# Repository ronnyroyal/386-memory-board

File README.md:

# 386 memory board by ronnyroy

This is an attempt to reproduce and improve the 32 bit memory expansion cards of the Intel 301 386 mainboard https://theretroweb.com/motherboards/s/intel-301-system-board-pba-451213-xxx based off my original 2MB card.  
Instead of 41256 DIP DRAM chips it uses 30pin SIMM modules, all SMD parts and can also be adapted to 8MB.  

Big thanks to i440bx who was working on reverse engineering his own card independently and helped greatly by finding the user manual for the board and an image of the 8MB card on https://www.vaxbarn.com/index.php?option=com_content&view=article&id=749.

# Initial Revision
The initial PCB revision has been tested and confirmed working.  
It was designed to test my clone of the 2MB card and for modding it to 8MB.

### Modding to 8MB
- CPUA21(pin85) on the slot to pin 5 of U9 and U16.  
- CPUA22(pin95) on the slot to pin 4 of U10 and U13.

# Second Revision
This adds the missing traces and jumpers required for 2/8MB operation and the slot cutout i excluded from rev.1.  

# Important!
An 8MB card configured to 2MB on the mainboard will start up fine and even pass an extended CheckIt memory test but running programs that use the memory of the card crash.  
So the card needs to be configured matching to the mainboard.

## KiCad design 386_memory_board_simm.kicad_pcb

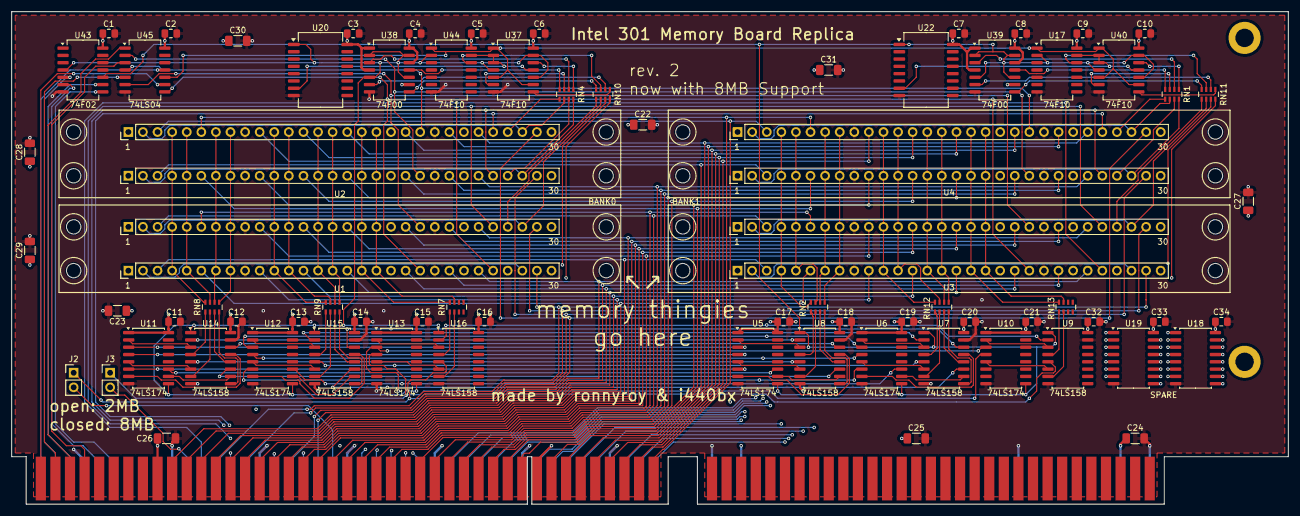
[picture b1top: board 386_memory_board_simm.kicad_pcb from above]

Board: 4 copper layers, 222.2 x 85.7 mm, 77 parts (0 on the bottom side), 174 nets.

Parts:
C1, C2, C3, C4, C5, C6, C7, C8, C9, C10, C11, C12, C13, C14, C15, C16, C17, C18, C19, C20, C21, C32, C33, C34: 100nF; C_0805_2012Metric_Pad1.18x1.45mm_HandSolder
C22, C23, C24, C25, C26, C27, C28, C29, C30, C31: 10µF; C_1206_3216Metric_Pad1.33x1.80mm_HandSolder
H1, H2: MountingHole; MountingHole_3.2mm_M3_DIN965_Pad
J1: Bus_386_Memory; BUS_386_MEMORY
J2, J3: Conn_01x02_Pin; PinHeader_1x02_P2.54mm_Vertical
RN1, RN2, RN4, RN7, RN8, RN9, RN10, RN11, RN12, RN13: 33Ω; R_Array_Concave_4x0603
U1, U2, U3, U4: DOUBLE-SIMM-30
U5, U6, U10, U11, U12, U13: 74LS174; SO-16_5.3x10.2mm_P1.27mm
U7, U8, U9, U14, U15, U16: 74LS158; SO-16_5.3x10.2mm_P1.27mm
U17, U37, U40, U44: 74F10; SO-14_5.3x10.2mm_P1.27mm
U18, U19: SPARE; SO-16_5.3x10.2mm_P1.27mm
U20, U22: SOIC-16W_7.5x12.8mm_P1.27mm
U38, U39: 74F00; SO-14_5.3x10.2mm_P1.27mm
U43: 74F02; SO-14_5.3x10.2mm_P1.27mm
U45: 74LS04; SO-14_5.3x10.2mm_P1.27mm

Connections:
A0A: J1.63 (CPUA3), U8.2 (I0a), U14.2 (I0a)
A0B: J1.70 (CPUA12), U5.3 (D0), U11.3 (D0)
A0B0: RN8.8 (R1.2), U1.4A (A0A), U1.4B (A0B), U2.4A (A0A), U2.4B (A0B)
A0B1: RN2.8 (R1.2), U3.4A (A0A), U3.4B (A0B), U4.4A (A0A), U4.4B (A0B)
A1A: J1.64 (CPUA4), U8.5 (I0b), U14.5 (I0b)
A1B: J1.71 (CPUA13), U5.4 (D1), U11.4 (D1)
A1B0: RN8.7 (R2.2), U1.5A (A1A), U1.5B (A1B), U2.5A (A1A), U2.5B (A1B)
A1B1: RN2.7 (R2.2), U3.5A (A1A), U3.5B (A1B), U4.5A (A1A), U4.5B (A1B)
A2A: J1.65 (CPUA5), U8.14 (I0c), U14.14 (I0c)
A2B: J1.73 (CPUA14), U5.6 (D2), U11.6 (D2)
A2B0: RN8.6 (R3.2), U1.7A (A2A), U1.7B (A2B), U2.7A (A2A), U2.7B (A2B)
A2B1: RN2.6 (R3.2), U3.7A (A2A), U3.7B (A2B), U4.7A (A2A), U4.7B (A2B)
A3A: J1.67 (CPUA6), U8.11 (I0d), U14.11 (I0d)
A3B: J1.74 (CPUA15), U5.11 (D3), U11.11 (D3)
A3B0: RN8.5 (R4.2), U1.8A (A3A), U1.8B (A3B), U2.8A (A3A), U2.8B (A3B)
A3B1: RN2.5 (R4.2), U3.8A (A3A), U3.8B (A3B), U4.8A (A3A), U4.8B (A3B)
A4A: J1.68 (CPUA7), U7.2 (I0a), U15.2 (I0a)
A4B: J1.75 (CPUA16), U6.3 (D0), U12.3 (D0)
A4B0: RN9.8 (R1.2), U1.11A (A4A), U1.11B (A4B), U2.11A (A4A), U2.11B (A4B)
A4B1: RN12.8 (R1.2), U3.11A (A4A), U3.11B (A4B), U4.11A (A4A), U4.11B (A4B)
A5A: J1.81 (RA8), U7.5 (I0b), U15.5 (I0b)
A5B: J1.76 (CPUA17), U6.4 (D1), U12.4 (D1)
A5B0: RN9.7 (R2.2), U1.12A (A5A), U1.12B (A5B), U2.12A (A5A), U2.12B (A5B)
A5B1: RN12.7 (R2.2), U3.12A (A5A), U3.12B (A5B), U4.12A (A5A), U4.12B (A5B)
A6A: J1.82 (RA9), U7.14 (I0c), U15.14 (I0c)
A6B: J1.77 (CPUA18), U6.6 (D2), U12.6 (D2)
A6B0: RN9.6 (R3.2), U1.14A (A6A), U1.14B (A6B), U2.14A (A6A), U2.14B (A6B)
A6B1: RN12.6 (R3.2), U3.14A (A6A), U3.14B (A6B), U4.14A (A6A), U4.14B (A6B)
A7A: J1.83 (RA10), U7.11 (I0d), U15.11 (I0d)
A7B: J1.79 (CPUA19), U6.11 (D3), U12.11 (D3)
A7B0: RN9.5 (R4.2), U1.15A (A7A), U1.15B (A7B), U2.15A (A7A), U2.15B (A7B)
A7B1: RN12.5 (R4.2), U3.15A (A7A), U3.15B (A7B), U4.15A (A7A), U4.15B (A7B)
A8A: J1.69 (RA11), U9.2 (I0a), U16.2 (I0a)
A8B: J1.80 (CPUA20), U10.3 (D0), U13.3 (D0)
A8B0: RN7.8 (R1.2), U1.17A (A8A), U1.17B (A8B), U2.17A (A8A), U2.17B (A8B)
A8B1: RN13.8 (R1.2), U3.17A (A8A), U3.17B (A8B), U4.17A (A8A), U4.17B (A8B)
A9A: J2.1, U9.5 (I0b), U16.5 (I0b)
A9B: J3.1, U10.4 (D1), U13.4 (D1)
A9B0: RN7.7 (R2.2), U1.18A (A9A), U1.18B (A9B), U2.18A (A9A), U2.18B (A9B)
A9B1: RN13.7 (R2.2), U3.18A (A9A), U3.18B (A9B), U4.18A (A9A), U4.18B (A9B)
CPUA21: J1.85 (CPUA21), J2.2
CPUA22: J1.95 (CPUA22), J3.2
D0R0: J1.132 (EXPD24), U1.3A (D0A), U3.3A (D0A)
D0R1: J1.124 (EXPD16), U1.3B (D0B), U3.3B (D0B)
D0R2: J1.115 (EXPD8), U2.3A (D0A), U4.3A (D0A)
D0R3: J1.106 (EXPD0), U2.3B (D0B), U4.3B (D0B)
D1R0: J1.133 (EXPD25), U1.6A (D1A), U3.6A (D1A)
D1R1: J1.125 (EXPD17), U1.6B (D1B), U3.6B (D1B)
D1R2: J1.116 (EXPD9), U2.6A (D1A), U4.6A (D1A)
D1R3: J1.107 (EXPD1), U2.6B (D1B), U4.6B (D1B)
D2R0: J1.134 (EXPD26), U1.10A (D2A), U3.10A (D2A)
D2R1: J1.126 (EXPD18), U1.10B (D2B), U3.10B (D2B)
D2R2: J1.117 (EXPD10), U2.10A (D2A), U4.10A (D2A)
D2R3: J1.108 (EXPD2), U2.10B (D2B), U4.10B (D2B)
D3R0: J1.135 (EXPD27), U1.13A (D3A), U3.13A (D3A)
D3R1: J1.127 (EXPD19), U1.13B (D3B), U3.13B (D3B)
D3R2: J1.118 (EXPD11), U2.13A (D3A), U4.13A (D3A)
D3R3: J1.109 (EXPD3), U2.13B (D3B), U4.13B (D3B)
D4R0: J1.136 (EXPD28), U1.16A (D4A), U3.16A (D4A)
D4R1: J1.128 (EXPD20), U1.16B (D4B), U3.16B (D4B)
D4R2: J1.119 (EXPD12), U2.16A (D4A), U4.16A (D4A)
D4R3: J1.110 (EXPD4), U2.16B (D4B), U4.16B (D4B)
D5R0: J1.137 (EXPD29), U1.20A (D5A), U3.20A (D5A)
D5R1: J1.129 (EXPD21), U1.20B (D5B), U3.20B (D5B)
D5R2: J1.120 (EXPD13), U2.20A (D5A), U4.20A (D5A)
D5R3: J1.111 (EXPD5), U2.20B (D5B), U4.20B (D5B)
D6R0: J1.138 (EXPD30), U1.23A (D6A), U3.23A (D6A)
D6R1: J1.130 (EXPD22), U1.23B (D6B), U3.23B (D6B)
D6R2: J1.121 (EXPD14), U2.23A (D6A), U4.23A (D6A)
D6R3: J1.112 (EXPD6), U2.23B (D6B), U4.23B (D6B)
D7R0: J1.139 (EXPD31), U1.25A (D7A), U3.25A (D7A)
D7R1: J1.131 (EXPD23), U1.25B (D7B), U3.25B (D7B)
D7R2: J1.122 (EXPD15), U2.25A (D7A), U4.25A (D7A)
D7R3: J1.113 (EXPD7), U2.25B (D7B), U4.25B (D7B)
DIN8R0: J1.93 (PI24_31), U1.29A (P-INA), U3.29A (P-INA)
DIN8R1: J1.91 (PI16_23), U1.29B (P-INB), U3.29B (P-INB)
DIN8R2: J1.88 (PI8_15), U2.29A (P-INA), U4.29A (P-INA)
DIN8R3: J1.86 (PI0_7), U2.29B (P-INB), U4.29B (P-INB)
DOUT8R0: J1.94 (P024_31), U1.26A (P-OUTA), U3.26A (P-OUTA)
DOUT8R1: J1.92 (PO16_23), U1.26B (P-OUTB), U3.26B (P-OUTB)
DOUT8R2: J1.89 (PO8_15), U2.26A (P-OUTA), U4.26A (P-OUTA)
DOUT8R3: J1.87 (PO0_7), U2.26B (P-OUTB), U4.26B (P-OUTB)
MEMREF: J1.105 (MEMREF), U45.11
unnamed: RN1.1 (R1.1), U40.12
unnamed: RN1.2 (R2.1), U39.3
unnamed: RN1.3 (R3.1), U40.6
unnamed: RN1.4 (R4.1), U39.11
unnamed: RN2.1 (R1.1), U8.4 (Za)
unnamed: RN2.2 (R2.1), U8.7 (Zb)
unnamed: RN2.3 (R3.1), U8.12 (Zc)
unnamed: RN2.4 (R4.1), U8.9 (Zd)
unnamed: RN4.1 (R1.1), U37.12
unnamed: RN4.2 (R2.1), U38.3
unnamed: RN4.3 (R3.1), U37.6
unnamed: RN4.4 (R4.1), U38.11
unnamed: RN7.1 (R1.1), U16.4 (Za)
unnamed: RN7.2 (R2.1), U16.7 (Zb)
unnamed: RN8.1 (R1.1), U14.4 (Za)
unnamed: RN8.2 (R2.1), U14.7 (Zb)
unnamed: RN8.3 (R3.1), U14.12 (Zc)
unnamed: RN8.4 (R4.1), U14.9 (Zd)
unnamed: RN9.1 (R1.1), U15.4 (Za)
unnamed: RN9.2 (R2.1), U15.7 (Zb)
unnamed: RN9.3 (R3.1), U15.12 (Zc)
unnamed: RN9.4 (R4.1), U15.9 (Zd)
unnamed: RN10.1 (R1.1), U37.8
unnamed: RN10.2 (R2.1), U38.6
unnamed: RN10.3 (R3.1), U44.12
unnamed: RN10.4 (R4.1), U38.8
unnamed: RN11.1 (R1.1), U40.8
unnamed: RN11.2 (R2.1), U39.6
unnamed: RN11.3 (R3.1), U17.12
unnamed: RN11.4 (R4.1), U39.8
unnamed: RN12.1 (R1.1), U7.4 (Za)
unnamed: RN12.2 (R2.1), U7.7 (Zb)
unnamed: RN12.3 (R3.1), U7.12 (Zc)
unnamed: RN12.4 (R4.1), U7.9 (Zd)
unnamed: RN13.1 (R1.1), U9.4 (Za)
unnamed: RN13.2 (R2.1), U9.7 (Zb)
unnamed: U5.2 (Q0), U8.3 (I1a)
unnamed: U5.5 (Q1), U8.6 (I1b)
unnamed: U5.7 (Q2), U8.13 (I1c)
unnamed: U5.10 (Q3), U8.10 (I1d)
unnamed: U6.2 (Q0), U7.3 (I1a)
unnamed: U6.5 (Q1), U7.6 (I1b)
unnamed: U6.7 (Q2), U7.13 (I1c)
unnamed: U6.10 (Q3), U7.10 (I1d)
unnamed: U9.3 (I1a), U10.2 (Q0)
unnamed: U9.6 (I1b), U10.5 (Q1)
unnamed: U11.2 (Q0), U14.3 (I1a)
unnamed: U11.5 (Q1), U14.6 (I1b)
unnamed: U11.7 (Q2), U14.13 (I1c)
unnamed: U11.10 (Q3), U14.10 (I1d)
unnamed: U12.2 (Q0), U15.3 (I1a)
unnamed: U12.5 (Q1), U15.6 (I1b)
unnamed: U12.7 (Q2), U15.13 (I1c)
unnamed: U12.10 (Q3), U15.10 (I1d)
unnamed: U13.2 (Q0), U16.3 (I1a)
unnamed: U13.5 (Q1), U16.6 (I1b)
unnamed: U20.7 (TAP8), U37.2, U37.3, U37.11, U44.13
unnamed: U17.13, U22.7 (TAP8), U40.2, U40.3, U40.11
RMSEL0: J1.103 (RMSEL0), U43.9
RMSEL1: J1.104 (RMSEL1), U43.5
SLEB0: J1.100 (SLEB0), U43.8
SLEB1: J1.101 (SLEB1), U43.6
UNKN5: U11.9 (Cp), U12.9 (Cp), U13.9 (Cp), U14.1 (S), U15.1 (S), U16.1 (S), U20.1 (IN), U37.4, U37.10, U37.13, U38.2, U38.5, U38.10, U38.13, U43.4, U44.2
UNKN6: U5.9 (Cp), U6.9 (Cp), U7.1 (S), U8.1 (S), U9.1 (S), U10.9 (Cp), U17.2, U22.1 (IN), U39.2, U39.5, U39.10, U39.13, U40.4, U40.10, U40.13, U43.10
VCC: C1.1, C2.1, C3.1, C4.1, C5.1, C6.1, C7.1, C8.1, C9.1, C10.1, C11.1, C12.1, C13.1, C14.1, C15.1, C16.1, C17.1, C18.1, C19.1, C20.1, C21.1, C22.1, C23.1, C24.1, C25.1, C26.1, C27.1, C28.1, C29.1, C30.1, C31.1, C32.1, C33.1, C34.1, J1.3 (+5V), J1.29 (+5V), J1.78 (+5V), J1.114 (+5V), J1.140 (+5V), U1.1A (VCCA), U1.1B (VCCB), U1.30A (VCCA), U1.30B (VCCB), U2.1A (VCCA), U2.1B (VCCB), U2.30A (VCCA), U2.30B (VCCB), U3.1A (VCCA), U3.1B (VCCB), U3.30A (VCCA), U3.30B (VCCB), U4.1A (VCCA), U4.1B (VCCB), U4.30A (VCCA), U4.30B (VCCB), U5.1 (~Mr), U5.16 (VCC), U6.1 (~Mr), U6.16 (VCC), U7.16 (VCC), U8.16 (VCC), U9.16 (VCC), U10.1 (~Mr), U10.16 (VCC), U11.1 (~Mr), U11.16 (VCC), U12.1 (~Mr), U12.16 (VCC), U13.1 (~Mr), U13.16 (VCC), U14.16 (VCC), U15.16 (VCC), U16.16 (VCC), U17.14 (VCC), U18.16 (VCC), U19.16 (VCC), U20.16 (VCC), U22.16 (VCC), U37.14 (VCC), U38.1, U38.4, U38.9, U38.12, U38.14 (VCC), U39.1, U39.4, U39.9, U39.12, U39.14 (VCC), U40.14 (VCC), U43.14 (VCC), U44.14 (VCC), U45.14 (VCC)
VSS: C1.2, C2.2, C3.2, C4.2, C5.2, C6.2, C7.2, C8.2, C9.2, C10.2, C11.2, C12.2, C13.2, C14.2, C15.2, C16.2, C17.2, C18.2, C19.2, C20.2, C21.2, C22.2, C23.2, C24.2, C25.2, C26.2, C27.2, C28.2, C29.2, C30.2, C31.2, C32.2, C33.2, C34.2, J1.1 (GND), J1.10 (GND), J1.31 (GND), J1.66 (GND), J1.72 (GND), J1.84 (GND), J1.90 (GND), J1.96 (GND), J1.102 (GND), U1.9A (GNDA), U1.9B (GNDB), U1.22A (GNDA), U1.22B (GNDB), U2.9A (GNDA), U2.9B (GNDB), U2.22A (GNDA), U2.22B (GNDB), U3.9A (GNDA), U3.9B (GNDB), U3.22A (GNDA), U3.22B (GNDB), U4.9A (GNDA), U4.9B (GNDB), U4.22A (GNDA), U4.22B (GNDB), U5.8 (GND), U6.8 (GND), U7.8 (GND), U7.15 (E), U8.8 (GND), U8.15 (E), U9.8 (GND), U9.15 (E), U10.8 (GND), U11.8 (GND), U12.8 (GND), U13.8 (GND), U14.8 (GND), U14.15 (E), U15.8 (GND), U15.15 (E), U16.8 (GND), U16.15 (E), U17.7 (GND), U18.8 (GND), U19.8 (GND), U20.8 (VSS), U22.8 (VSS), U37.7 (GND), U38.7 (GND), U39.7 (GND), U40.7 (GND), U43.7 (GND), U44.7 (GND), U45.7 (GND)
WER0: J1.148 (WE_3), U45.9
WER1: J1.147 (WE_2), U45.5
WER2: J1.146 (WE_1), U45.1
WER3: J1.145 (WE_0), U45.3
~CASB0R0: RN10.8 (R1.2), U1.2A (~CASA), U1.28A (CASPA)
~CASB0R1: RN10.6 (R3.2), U1.2B (~CASB), U1.28B (CASPB)
~CASB0R2: RN4.8 (R1.2), U2.2A (~CASA), U2.28A (CASPA)
~CASB0R3: RN4.6 (R3.2), U2.2B (~CASB), U2.28B (CASPB)
~CASB1R0: RN11.8 (R1.2), U3.2A (~CASA), U3.28A (CASPA)
~CASB1R1: RN11.6 (R3.2), U3.2B (~CASB), U3.28B (CASPB)
~CASB1R2: RN1.8 (R1.2), U4.2A (~CASA), U4.28A (CASPA)
~CASB1R3: RN1.6 (R3.2), U4.2B (~CASB), U4.28B (CASPB)
~MEMREF: U17.1, U37.1, U37.5, U37.9, U40.1, U40.5, U40.9, U44.1, U45.10
~RASB0R0: RN10.7 (R2.2), U1.27A (~RASA)
~RASB0R1: RN10.5 (R4.2), U1.27B (~RASB)
~RASB0R2: RN4.7 (R2.2), U2.27A (~RASA)
~RASB0R3: RN4.5 (R4.2), U2.27B (~RASB)
~RASB1R0: RN11.7 (R2.2), U3.27A (~RASA)
~RASB1R1: RN11.5 (R4.2), U3.27B (~RASB)
~RASB1R2: RN1.7 (R2.2), U4.27A (~RASA)
~RASB1R3: RN1.5 (R4.2), U4.27B (~RASB)
~WER0: U1.21A (~WEA), U3.21A (~WEA), U45.8
~WER1: U1.21B (~WEB), U3.21B (~WEB), U45.6
~WER2: U2.21A (~WEA), U4.21A (~WEA), U45.2
~WER3: U2.21B (~WEB), U4.21B (~WEB), U45.4

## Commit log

2024-11-03 second routing pass completed
2024-11-03 card images added
2024-11-03 new card image added
2024-11-03 add license
2024-11-10 fixed footprint of delay lines
2024-11-20 added cosmetic silkscreen and fixed IC silkscreen
2024-11-20 added bracket mounting holes
2024-11-20 fixed bracket mounting holes
2024-11-20 new pcb image
2024-12-09 final touchups before ordering first boards
2025-01-09 Update readme with notes on first PCB revision and assembly
2025-01-09 add finished PCB image
2025-06-01 PCB Revision 2 -implements 8MB operation -fixed the missing slot cutout on rev.1 -overhauls the slot connector based on i440bx's discoveries and design -add information to modify rev.1 Boards to 8MB
2025-06-01 Add images of PCB rev.2
